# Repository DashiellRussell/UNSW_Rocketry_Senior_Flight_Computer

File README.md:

# UNSW Rocketry Senior Flight Computer

KiCad project for the senior flight computer used by UNSW Rocketry.

## Revisions

This repo holds each hardware revision in its own self-contained folder. Every
folder is a complete KiCad project (schematic, PCB, and its own copy of the
footprint library) so any revision can be opened and fabricated independently.

| Revision | Folder | Status |
| --- | --- | --- |
| **v0.0** | [`v0.0/`](v0.0/) | Frozen — known-good design. Do not edit. |
| **v1.0** | [`v1.0/`](v1.0/) | In progress — next revision (component + design changes). |

The exact v0.0 snapshot is also recoverable from the `v0.0` git tag
(`git checkout v0.0`).

> **Working on a new revision?** Copy the latest frozen folder to the next
> version number (e.g. `cp -R v1.0 v1.1`), then edit the copy. Tag the old one
> before you move on.

## Documents

Reference docs live in [`docs/`](docs/) and render inline on GitHub:

- [Schematic (PDF)](docs/UNSW_Rocketry_Senior_Flight_Computer.pdf) — exported full schematic (v0.0)
- [Project OZONE](docs/Project%20OZONE.pdf)

## Project layout (within each revision folder)

| File | Purpose |
| --- | --- |
| `UNSW_Rocketry_Senior_Flight_Computer.kicad_pro` | KiCad project file |
| `UNSW_Rocketry_Senior_Flight_Computer.kicad_sch` | Top-level schematic |
| `UNSW_Rocketry_Senior_Flight_Computer.kicad_pcb` | PCB layout |
| `Power.kicad_sch` | Power sheet |
| `Pyros.kicad_sch` | Pyrotechnic channels sheet |
| `Comms.kicad_sch` | Communications sheet |
| `Peripherals.kicad_sch` | Peripherals sheet |
| `Indication.kicad_sch` | Status / indication sheet |
| `UNSW_ROCKETRY_LIBRARY.pretty/` | Project-specific footprint library |
| `UNSW_Rocketry_Senior_Flight_Computer.csv` | BOM export |

## Opening the project

1. Install [KiCad 10.0](https://www.kicad.org/download/) or newer.
2. Clone this repo.
3. Open the `.kicad_pro` inside the revision folder you want, e.g.
   `v1.0/UNSW_Rocketry_Senior_Flight_Computer.kicad_pro`.

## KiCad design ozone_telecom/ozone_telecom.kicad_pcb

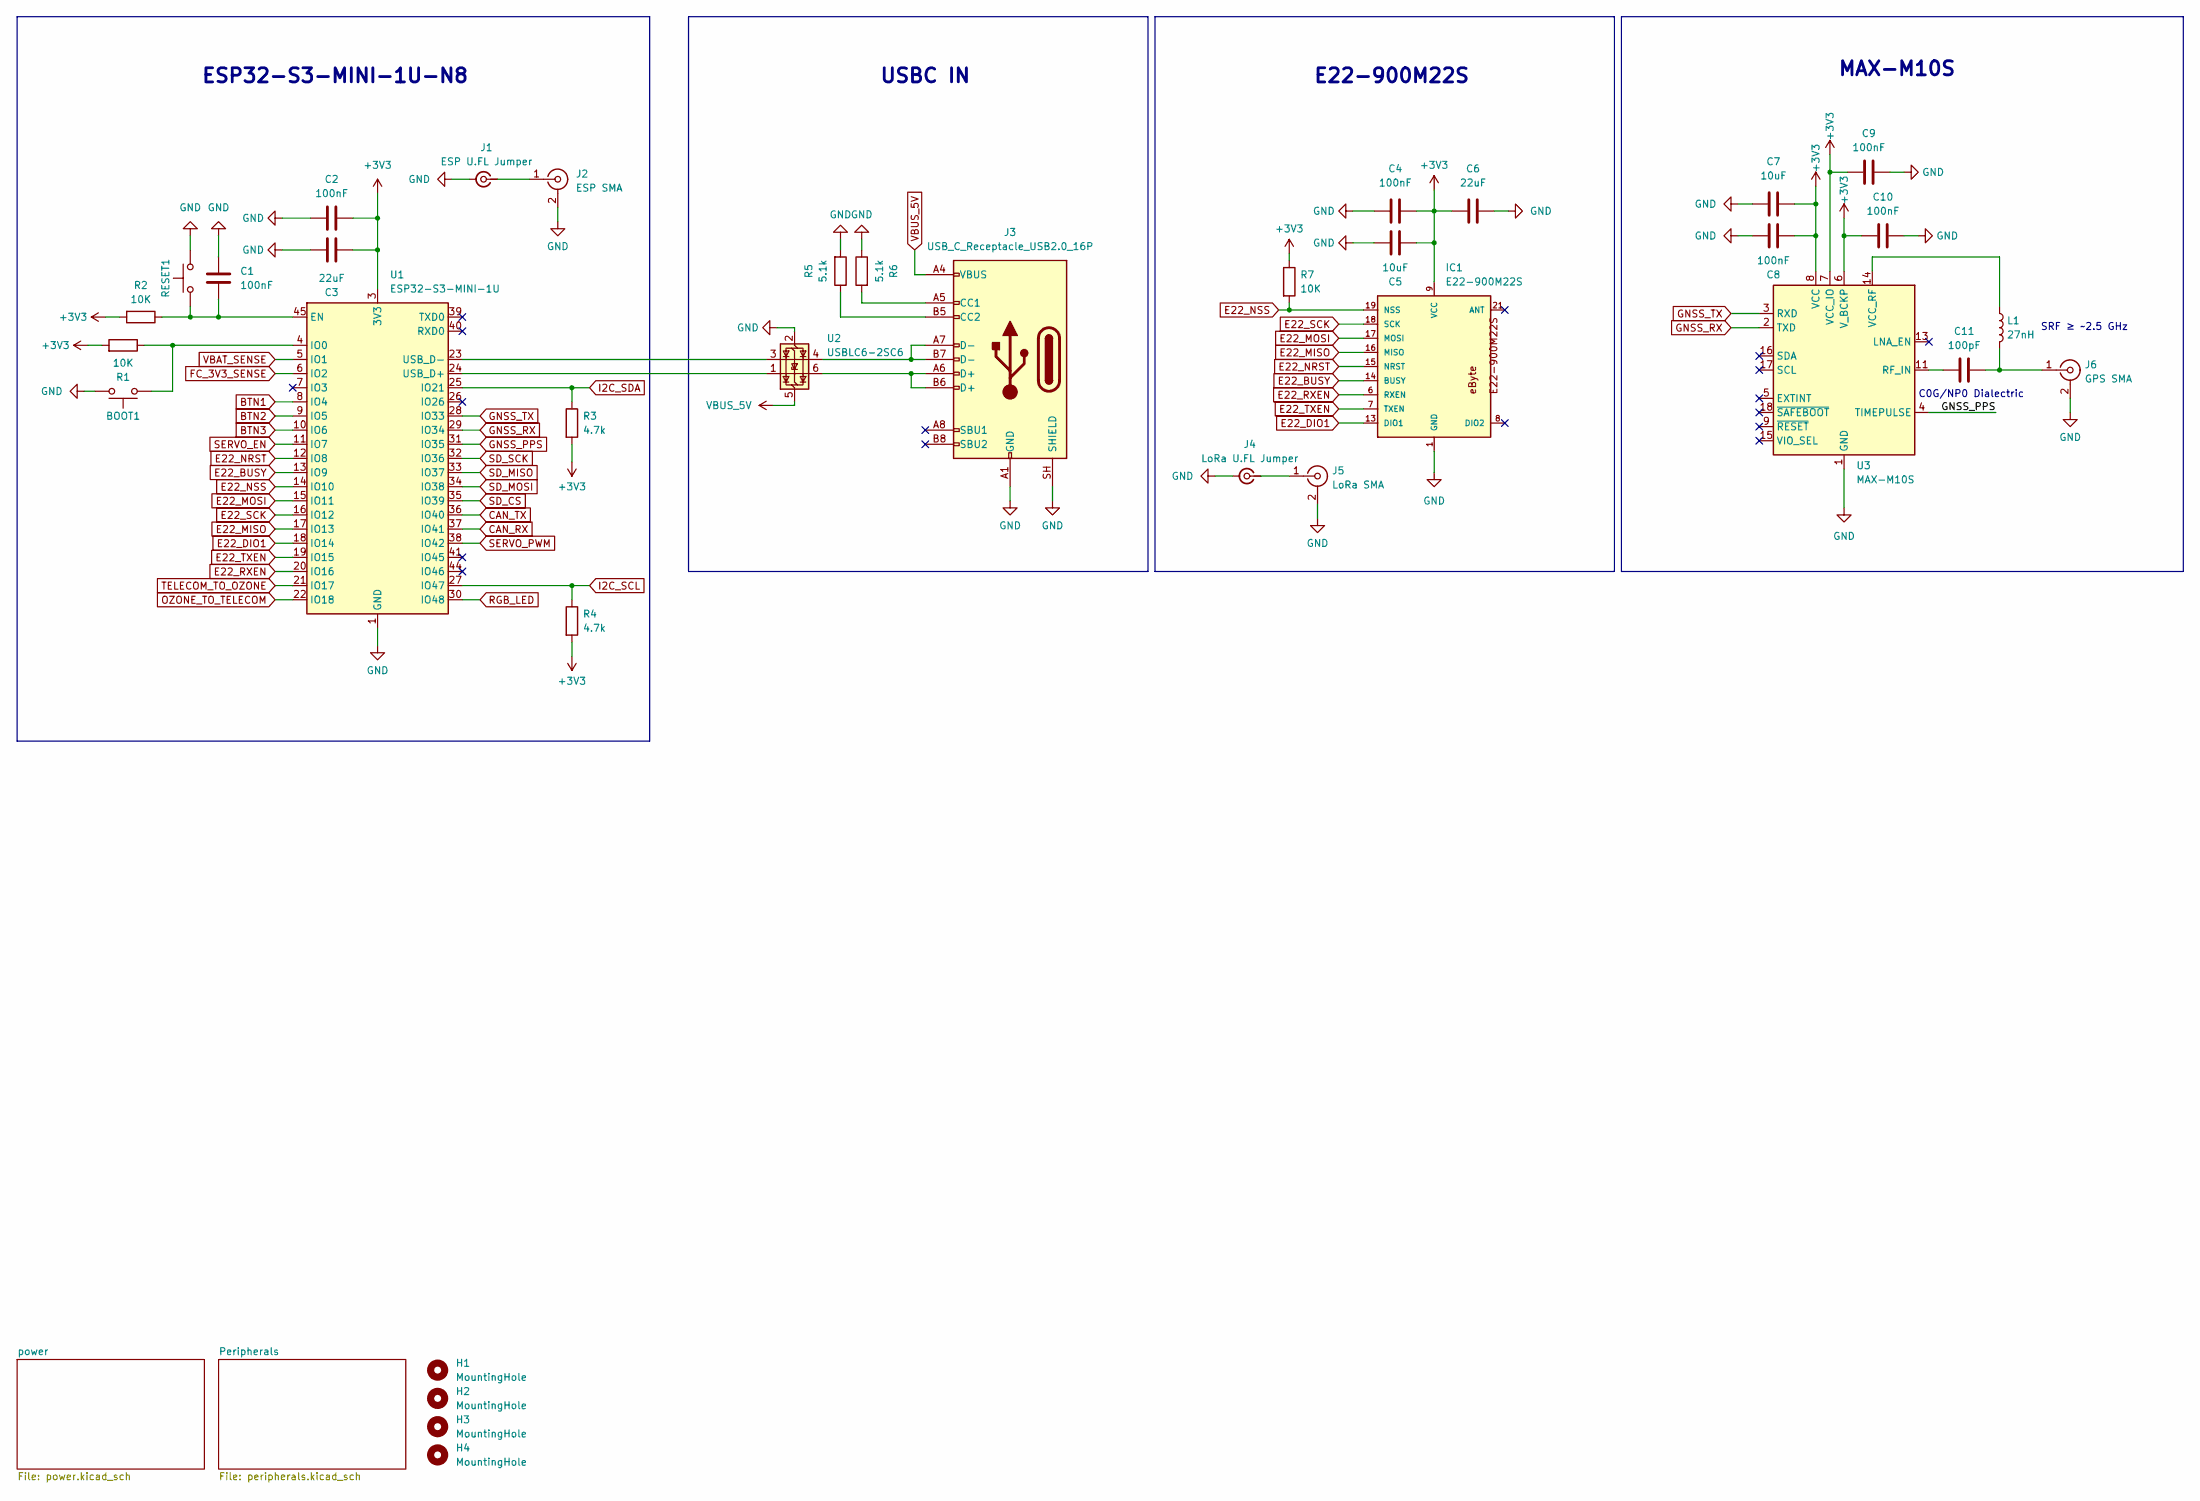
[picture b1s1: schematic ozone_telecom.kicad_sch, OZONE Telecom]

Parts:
BOOT1: SMD_4.6x2.8mm_h1.9mm; Push_SMD_4.6x2.8mm_h1.9mm
C1: 100nF; C_0603_1608Metric
C2, C4, C8, C9, C10: 100nF; C_0805_2012Metric
C3, C6: 22uF; C_0805_2012Metric
C5, C7: 10uF; C_0805_2012Metric
C11: 100pF; C_0603_1608Metric
H1, H2, H3, H4: MountingHole; MountingHole_3.2mm_M3_DIN965_Pad
IC1: E22-900M22S
J1: ESP U.FL Jumper; U.FL_Hirose_U.FL-R-SMT-1_Vertical
J2: ESP SMA; SMA_Amphenol_132289_EdgeMount
J3: USB_C_Receptacle_USB2.0_16P; USB_C_Receptacle_GCT_USB4085
J4: LoRa U.FL Jumper; U.FL_Hirose_U.FL-R-SMT-1_Vertical
J5: LoRa SMA; SMA_Amphenol_132289_EdgeMount
J6: GPS SMA; SMA_Amphenol_132289_EdgeMount
L1: 27nH; L_0603_1608Metric
R1, R2, R7: 10K; R_0603_1608Metric
R3, R4: 4.7k; R_0603_1608Metric
R5, R6: 5.1k; R_0603_1608Metric
RESET1: SMD_4.6x2.8mm_h1.9mm; Push_SMD_4.6x2.8mm_h1.9mm
U1: ESP32-S3-MINI-1U; ESP32-S2-MINI-1U
U2: USBLC6-2SC6; SOT-23-6
U3: MAX-M10S; ublox_MAX

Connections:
+3V3: C2.1, C3.1, C4.2, C5.2, C6.1, C7.1, C8.1, C9.2, C10.2, IC1.9 (VCC), R1.2, R2.2, R3.2, R4.2, R7.1, U1.3 (3V3), U3.6 (V_BCKP), U3.7 (VCC_IO), U3.8 (VCC); also elsewhere on the board
BTN1: U1.8 (IO4); also elsewhere on the board
BTN2: U1.9 (IO5); also elsewhere on the board
BTN3: U1.10 (IO6); also elsewhere on the board
CAN_RX: U1.37 (IO41); also elsewhere on the board
CAN_TX: U1.36 (IO40); also elsewhere on the board
E22_BUSY: IC1.14 (BUSY), U1.13 (IO9)
E22_DIO1: IC1.13 (DIO1), U1.18 (IO14)
E22_MISO: IC1.16 (MISO), U1.17 (IO13)
E22_MOSI: IC1.17 (MOSI), U1.15 (IO11)
E22_NRST: IC1.15 (NRST), U1.12 (IO8)
E22_NSS: IC1.19 (NSS), R7.2, U1.14 (IO10)
E22_RXEN: IC1.6 (RXEN), U1.20 (IO16)
E22_SCK: IC1.18 (SCK), U1.16 (IO12)
E22_TXEN: IC1.7 (TXEN), U1.19 (IO15)
FC_3V3_SENSE: U1.6 (IO2); also elsewhere on the board
GND: BOOT1.2, C1.1, C2.2, C3.2, C4.1, C5.1, C6.2, C7.2, C8.2, C9.1, C10.1, IC1.1 (GND), IC1.2 (GND), IC1.3 (GND), IC1.4 (GND), IC1.5 (GND), IC1.10 (GND), IC1.11 (GND), IC1.12 (GND), IC1.20 (GND), IC1.22 (GND), J1.2 (Ext), J2.2 (Ext), J3.A1 (GND), J3.A12 (GND), J3.B1 (GND), J3.B12 (GND), J3.SH (SHIELD), J4.2 (Ext), J5.2 (Ext), J6.2 (Ext), R5.2, R6.1, RESET1.1, U1.1 (GND), U1.2 (GND), U1.42 (GND), U1.43 (GND), U1.46 (GND), U1.47 (GND), U1.48 (GND), U1.49 (GND), U1.50 (GND), U1.51 (GND), U1.52 (GND), U1.53 (GND), U1.54 (GND), U1.55 (GND), U1.56 (GND), U1.57 (GND), U1.58 (GND), U1.59 (GND), U1.60 (GND), U1.61 (GND), U1.62 (GND), U1.63 (GND), U1.64 (GND), U1.65 (GND), U2.2 (GND), U3.1 (GND), U3.10 (GND), U3.12 (GND); also elsewhere on the board
GNSS_PPS: U1.31 (IO35), U3.4 (TIMEPULSE)
GNSS_RX: U1.29 (IO34), U3.2 (TXD)
GNSS_TX: U1.28 (IO33), U3.3 (RXD)
I2C_SCL: R4.1, U1.27 (IO47); also elsewhere on the board
I2C_SDA: R3.1, U1.25 (IO21); also elsewhere on the board
unnamed: J1.1 (In), J2.1 (In)
unnamed: J3.A5 (CC1), R6.2
unnamed: J3.B5 (CC2), R5.1
unnamed: J3.A6 (D+), J3.B6 (D+), U2.6 (I/O1)
unnamed: J3.A7 (D-), J3.B7 (D-), U2.4 (I/O2)
unnamed: J4.1 (In), J5.1 (In)
unnamed: C11.1, J6.1 (In), L1.2
unnamed: C1.2, R2.1, RESET1.2, U1.45 (EN)
unnamed: BOOT1.1, R1.1, U1.4 (IO0)
unnamed: U1.24 (USB_D+), U2.1 (I/O1)
unnamed: U1.23 (USB_D-), U2.3 (I/O2)
unnamed: C11.2, U3.11 (RF_IN)
unnamed: L1.1, U3.14 (VCC_RF)
OZONE_TO_TELECOM: U1.22 (IO18); also elsewhere on the board
RGB_LED: U1.30 (IO48); also elsewhere on the board
SD_CS: U1.35 (IO39); also elsewhere on the board
SD_MISO: U1.33 (IO37); also elsewhere on the board
SD_MOSI: U1.34 (IO38); also elsewhere on the board
SD_SCK: U1.32 (IO36); also elsewhere on the board
SERVO_EN: U1.11 (IO7); also elsewhere on the board
SERVO_PWM: U1.38 (IO42); also elsewhere on the board
TELECOM_TO_OZONE: U1.21 (IO17); also elsewhere on the board
VBAT_SENSE: U1.5 (IO1); also elsewhere on the board
VBUS_5V: J3.A4 (VBUS), J3.A9 (VBUS), J3.B4 (VBUS), J3.B9 (VBUS), U2.5 (VBUS); also elsewhere on the board

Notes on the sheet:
SRF ≥ ~2.5 GHz
E22-900M22S
C0G/NP0 Dialectric
ESP32-S3-MINI-1U-N8
MAX-M10S
USBC IN

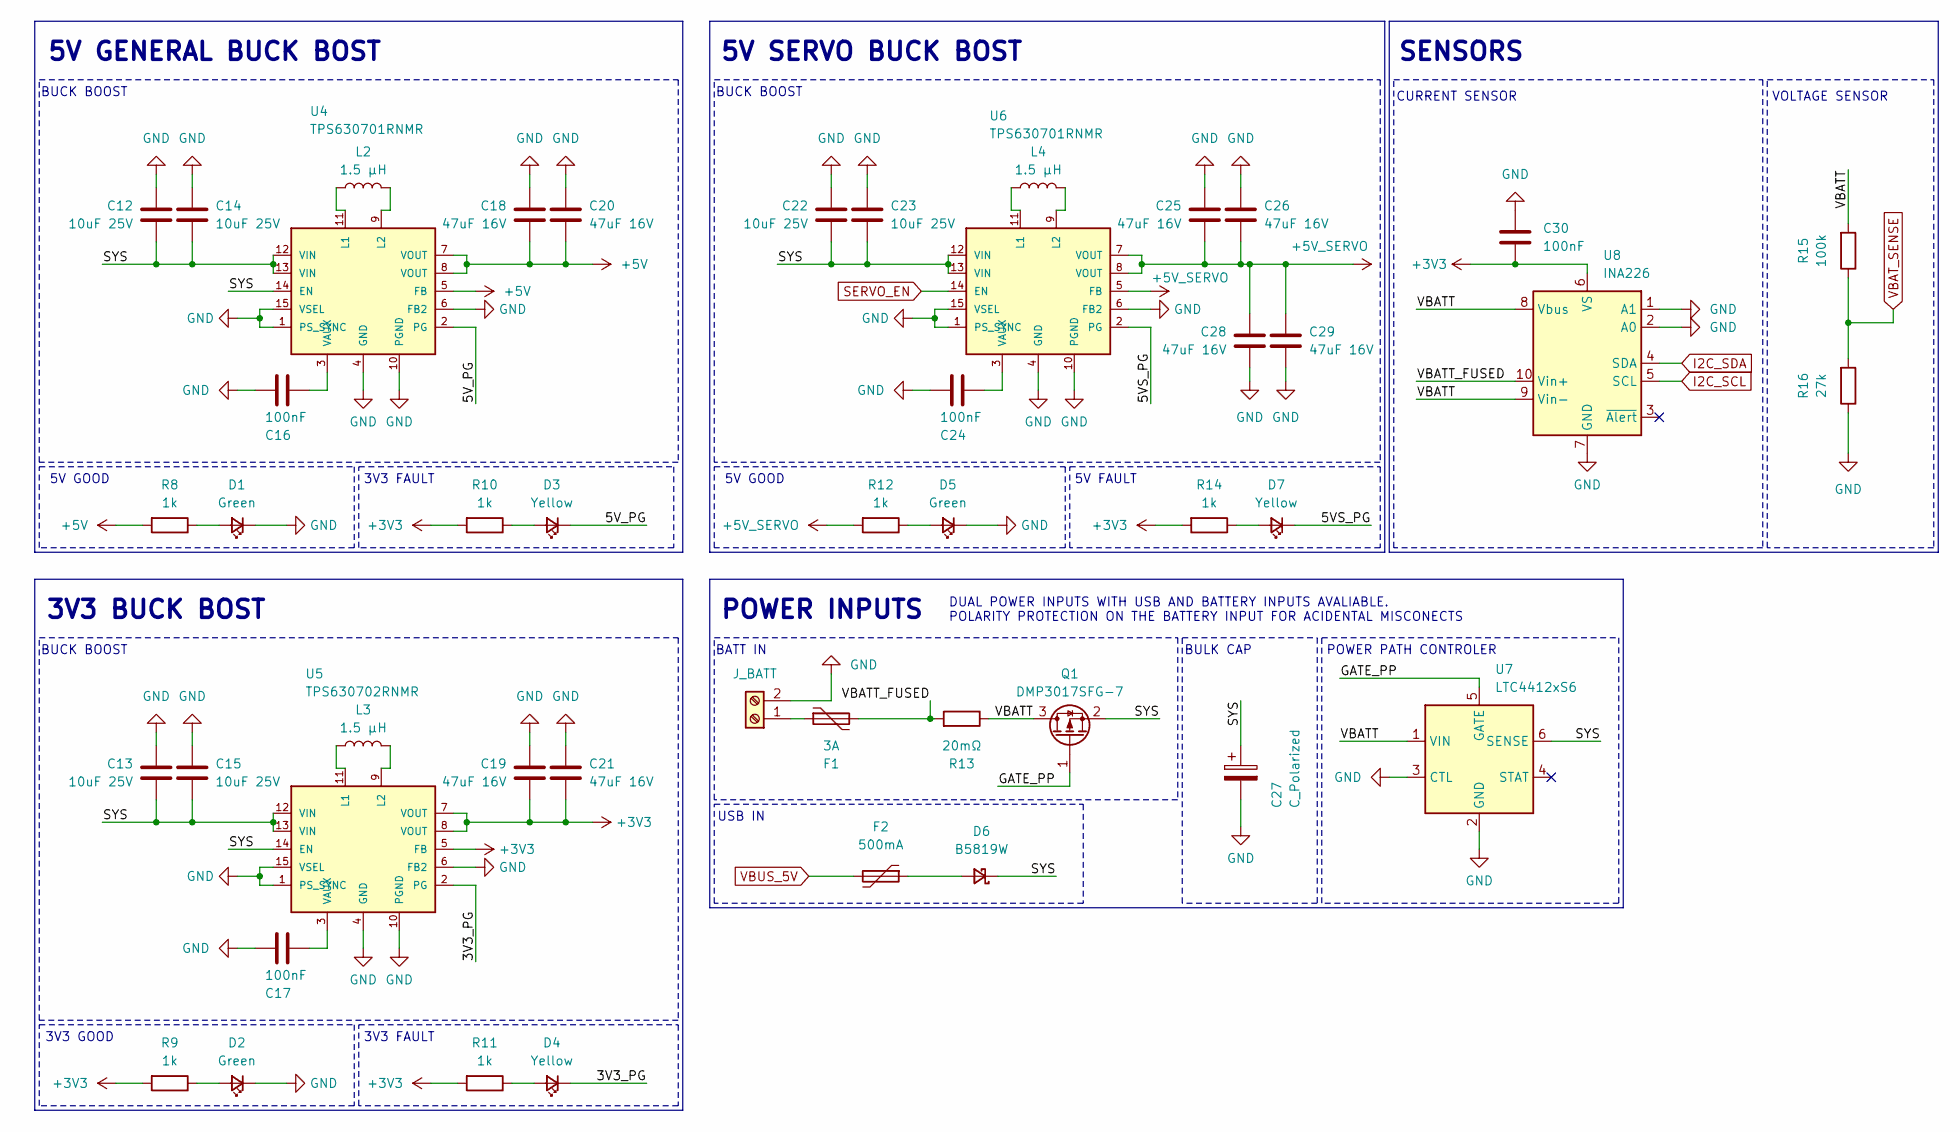
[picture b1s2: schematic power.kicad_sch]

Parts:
C12, C13, C14, C15, C22, C23: 10uF 25V; C_0805_2012Metric
C16, C17, C24, C30: 100nF; C_0805_2012Metric
C18, C19, C20, C21, C25, C26, C28, C29: 47uF 16V; C_0805_2012Metric
C27: C_Polarized; CP_Elec_6.3x5.4
D1, D2, D5: Green; LED_0603_1608Metric_Green
D3, D4, D7: Yellow; LED_0603_1608Metric_Yellow
D6: B5819W; D_SOD-123
F1: 3A; Fuse_1206_3216Metric
F2: 500mA; Fuse_1206_3216Metric
J7: J_BATT; TerminalBlock_Phoenix_PT-1,5-2-3.5-H_1x02_P3.50mm_Horizontal
L2, L3, L4: 1.5 µH; L_Coilcraft_XxL4020
Q1: DMP3017SFG-7; SOT-23
R8, R9, R10, R11, R12, R14: 1k; R_0603_1608Metric
R13: 20mΩ; R_2512_6332Metric
R15: 100k; R_0603_1608Metric
R16: 27k; R_0603_1608Metric
U4, U6: TPS630701RNMR; RNM0015A
U5: TPS630702RNMR; RNM0015A
U7: LTC4412xS6; TSOT-23-6
U8: INA226; TSSOP-10_3x3mm_P0.5mm

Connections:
+3V3: C19.2, C21.2, C30.2, R9.2, R10.2, R11.2, R14.2, U5.5 (FB), U5.7 (VOUT), U5.8 (VOUT), U8.6 (VS); also elsewhere on the board
+5V: C18.2, C20.2, R8.2, U4.5 (FB), U4.7 (VOUT), U4.8 (VOUT); also elsewhere on the board
+5V_SERVO: C25.2, C26.2, C28.1, C29.1, R12.2, U6.5 (FB), U6.7 (VOUT), U6.8 (VOUT); also elsewhere on the board
/power/3V3_PG: D4.1 (K), U5.2 (PG)
/power/5VS_PG: D7.1 (K), U6.2 (PG)
/power/5V_PG: D3.1 (K), U4.2 (PG)
/power/GATE_PP: Q1.1 (G), U7.5 (GATE)
/power/SYS: C12.2, C13.2, C14.2, C15.2, C22.2, C23.2, C27.1, D6.1 (K), Q1.2 (S), U4.12 (VIN), U4.13 (VIN), U4.14 (EN), U5.12 (VIN), U5.13 (VIN), U5.14 (EN), U6.12 (VIN), U6.13 (VIN), U7.6 (SENSE)
/power/VBATT: Q1.3 (D), R13.1, R15.2, U7.1 (VIN), U8.8 (Vbus), U8.9 (Vin-)
/power/VBATT_FUSED: F1.2, R13.2, U8.10 (Vin+)
GND: C12.1, C13.1, C14.1, C15.1, C16.2, C17.2, C18.1, C19.1, C20.1, C21.1, C22.1, C23.1, C24.2, C25.1, C26.1, C27.2, C28.2, C29.2, C30.1, D1.1 (K), D2.1 (K), D5.1 (K), J7.2, R16.1, U4.1 (PS_SYNC), U4.4 (GND), U4.6 (FB2), U4.10 (PGND), U4.15 (VSEL), U5.1 (PS_SYNC), U5.4 (GND), U5.6 (FB2), U5.10 (PGND), U5.15 (VSEL), U6.1 (PS_SYNC), U6.4 (GND), U6.6 (FB2), U6.10 (PGND), U6.15 (VSEL), U7.2 (GND), U7.3 (CTL), U8.1 (A1), U8.2 (A0), U8.7 (GND); also elsewhere on the board
I2C_SCL: U8.5 (SCL); also elsewhere on the board
I2C_SDA: U8.4 (SDA); also elsewhere on the board
unnamed: D1.2 (A), R8.1
unnamed: D2.2 (A), R9.1
unnamed: D3.2 (A), R10.1
unnamed: D4.2 (A), R11.1
unnamed: D5.2 (A), R12.1
unnamed: D6.2 (A), F2.1
unnamed: D7.2 (A), R14.1
unnamed: F1.1, J7.1
unnamed: L2.1, U4.11 (L1)
unnamed: L2.2, U4.9 (L2)
unnamed: C16.1, U4.3 (VAUX)
unnamed: L3.1, U5.11 (L1)
unnamed: L3.2, U5.9 (L2)
unnamed: C17.1, U5.3 (VAUX)
unnamed: L4.1, U6.11 (L1)
unnamed: L4.2, U6.9 (L2)
unnamed: C24.1, U6.3 (VAUX)
SERVO_EN: U6.14 (EN); also elsewhere on the board
VBAT_SENSE: R15.1, R16.2; also elsewhere on the board
VBUS_5V: F2.2; also elsewhere on the board

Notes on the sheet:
POWER PATH CONTROLER
VOLTAGE SENSOR
SENSORS
5V FAULT
BUCK BOOST
3V3 FAULT
BATT IN
3V3 GOOD
3V3 BUCK BOST
5V GOOD
USB IN
BULK CAP
POWER INPUTS
CURRENT SENSOR
5V GENERAL BUCK BOST
5V SERVO BUCK BOST
DUAL POWER INPUTS WITH USB AND BATTERY INPUTS AVALIABLE. POLARITY PROTECTION ON THE BATTERY INPUT FOR ACIDENTAL MISCONECTS

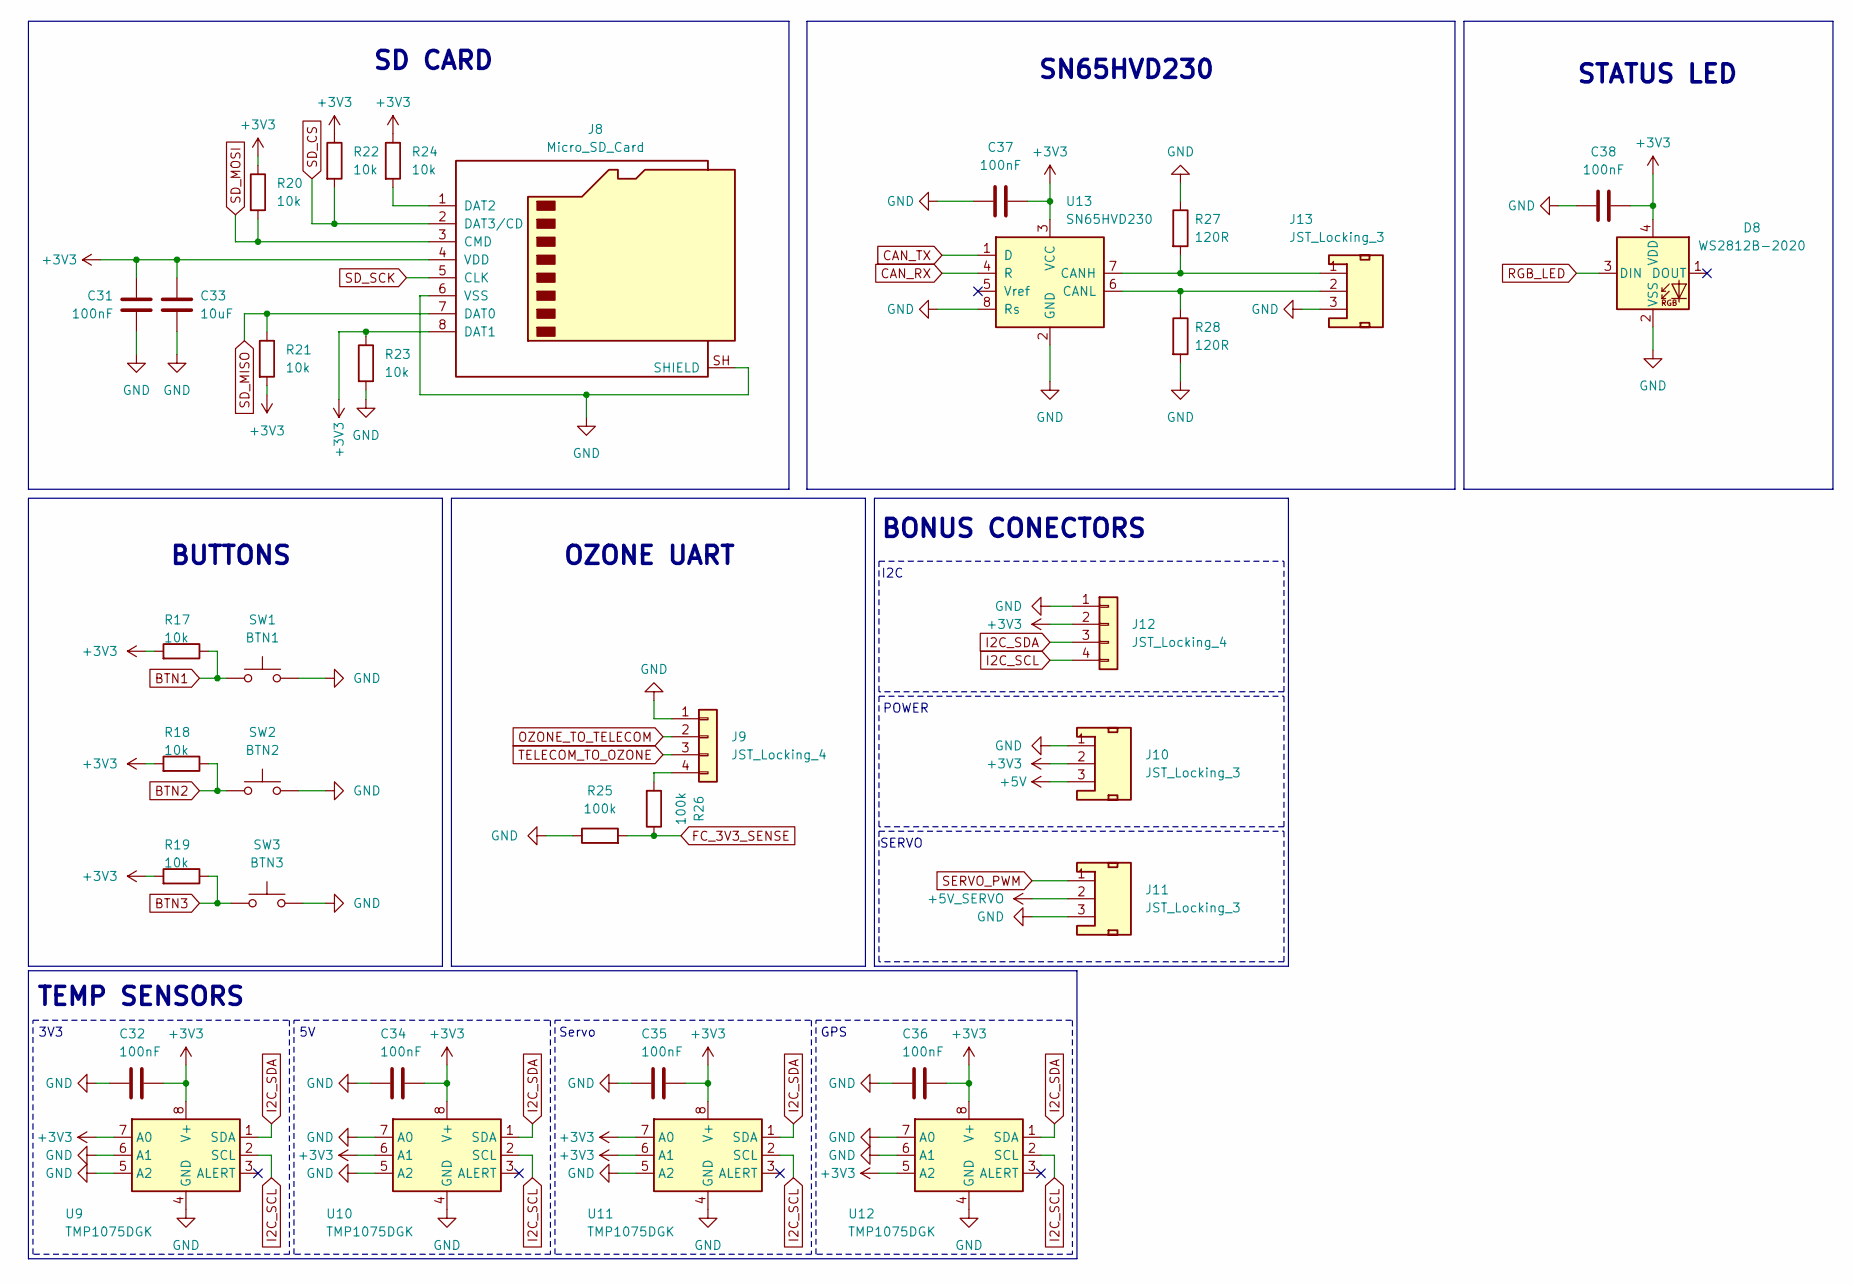
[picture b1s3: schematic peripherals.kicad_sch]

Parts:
C31, C32, C34, C35, C36: 100nF; C_0805_2012Metric
C33: 10uF; C_0805_2012Metric
C37, C38: 100nF; C_0603_1608Metric
D8: WS2812B-2020; LED_WS2812B-2020_PLCC4_2.0x2.0mm
J8: Micro_SD_Card; microSD_HC_Molex_47219-2001
J9, J12: JST_Locking_4; JST_1x04_P1.25mm_Locking_Horizontal_SMD
J10, J11, J13: JST_Locking_3; JST_1x03_P1.25mm_Locking_Horizontal_SMD
R17, R18, R19, R20, R21, R22, R23, R24: 10k; R_0603_1608Metric
R25, R26: 100k; R_0603_1608Metric
R27, R28: 120R; C_0805_2012Metric
SW1: BTN1; SW_Push_1P1T_NO_CK_KMR2
SW2: BTN2; SW_Push_1P1T_NO_CK_KMR2
SW3: BTN3; SW_Push_1P1T_NO_CK_KMR2
U9, U10, U11, U12: TMP1075DGK; VSSOP-8_3x3mm_P0.65mm
U13: SN65HVD230; SOIC-8_3.9x4.9mm_P1.27mm

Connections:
+3V3: C31.1, C32.1, C33.1, C34.1, C35.1, C36.1, C37.1, C38.1, D8.4 (VDD), J8.4 (VDD), J8.8 (DAT1), J10.2, J12.2, R17.2, R18.2, R19.2, R20.1, R21.2, R22.1, R23.1, R24.1, U9.7 (A0), U9.8 (V+), U10.6 (A1), U10.8 (V+), U11.6 (A1), U11.7 (A0), U11.8 (V+), U12.5 (A2), U12.8 (V+), U13.3 (VCC); also elsewhere on the board
+5V: J10.3; also elsewhere on the board
+5V_SERVO: J11.2; also elsewhere on the board
BTN1: R17.1, SW1.1; also elsewhere on the board
BTN2: R18.1, SW2.1; also elsewhere on the board
BTN3: R19.1, SW3.1; also elsewhere on the board
CAN_RX: U13.4 (R); also elsewhere on the board
CAN_TX: U13.1 (D); also elsewhere on the board
FC_3V3_SENSE: R25.2, R26.1; also elsewhere on the board
GND: C31.2, C32.2, C33.2, C34.2, C35.2, C36.2, C37.2, C38.2, D8.2 (VSS), J8.6 (VSS), J8.SH (SHIELD), J9.1, J10.1, J11.3, J12.1, J13.3, R23.2, R25.1, R27.1, R28.2, SW1.2, SW2.2, SW3.2, U9.4 (GND), U9.5 (A2), U9.6 (A1), U10.4 (GND), U10.5 (A2), U10.7 (A0), U11.4 (GND), U11.5 (A2), U12.4 (GND), U12.6 (A1), U12.7 (A0), U13.2 (GND), U13.8 (Rs); also elsewhere on the board
I2C_SCL: J12.4, U9.2 (SCL), U10.2 (SCL), U11.2 (SCL), U12.2 (SCL); also elsewhere on the board
I2C_SDA: J12.3, U9.1 (SDA), U10.1 (SDA), U11.1 (SDA), U12.1 (SDA); also elsewhere on the board
unnamed: J8.1 (DAT2), R24.2
unnamed: J9.4, R26.2
unnamed: J13.1, R27.2, U13.7 (CANH)
unnamed: J13.2, R28.1, U13.6 (CANL)
OZONE_TO_TELECOM: J9.2; also elsewhere on the board
RGB_LED: D8.3 (DIN); also elsewhere on the board
SD_CS: J8.2 (DAT3/CD), R22.2; also elsewhere on the board
SD_MISO: J8.7 (DAT0), R21.1; also elsewhere on the board
SD_MOSI: J8.3 (CMD), R20.2; also elsewhere on the board
SD_SCK: J8.5 (CLK); also elsewhere on the board
SERVO_PWM: J11.1; also elsewhere on the board
TELECOM_TO_OZONE: J9.3; also elsewhere on the board

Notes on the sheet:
STATUS LED
Servo
BONUS CONECTORS
TEMP SENSORS
I2C
POWER
3V3
BUTTONS
SN65HVD230
OZONE UART
SD CARD
SERVO
GPS

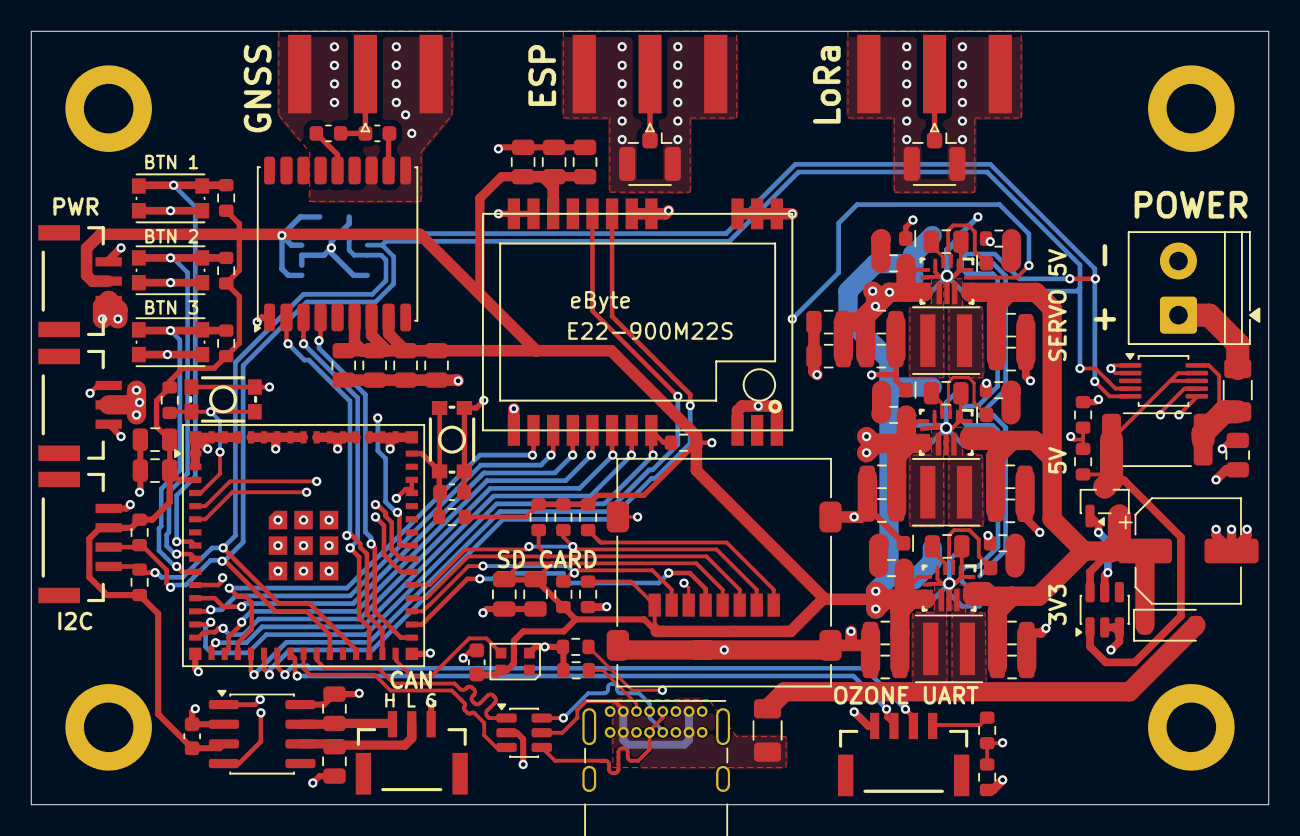
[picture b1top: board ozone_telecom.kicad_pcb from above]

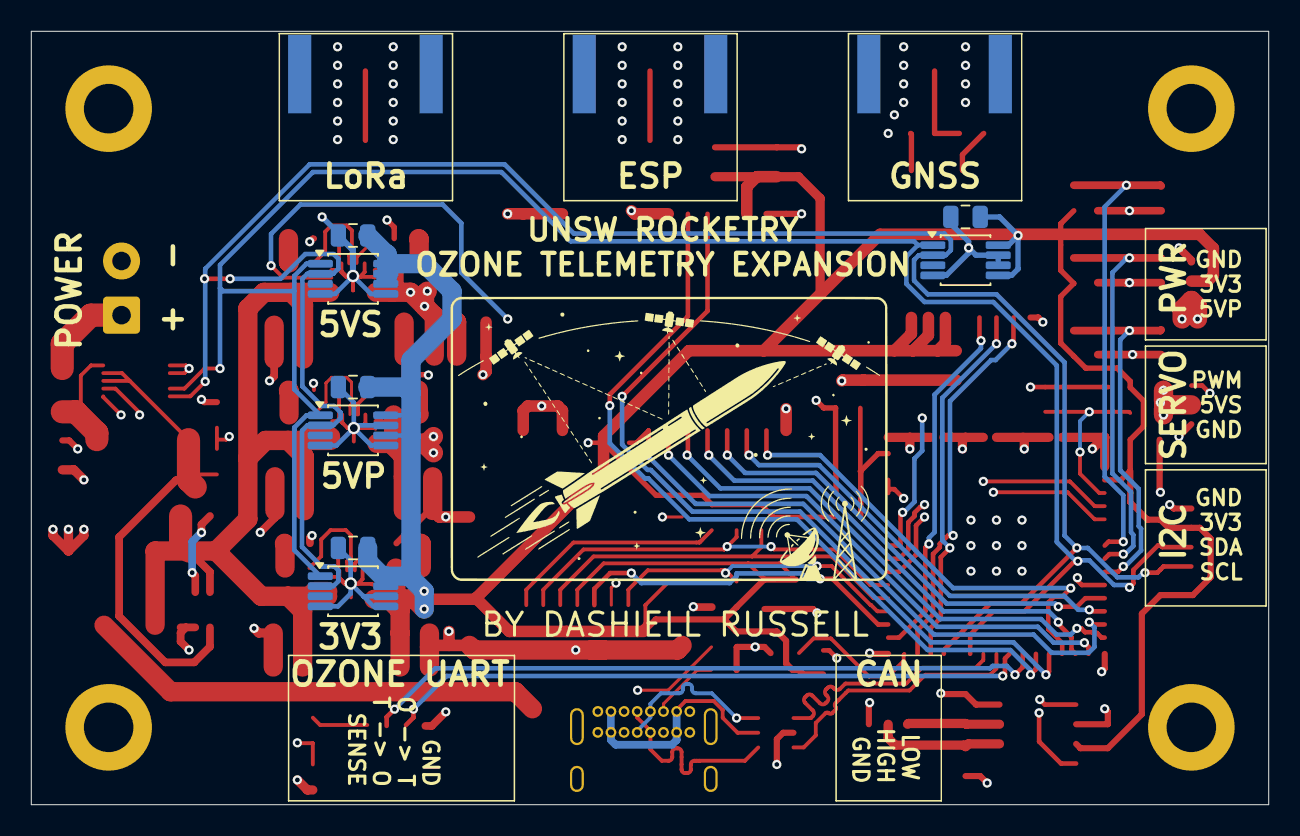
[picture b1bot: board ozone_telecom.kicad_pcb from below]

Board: 4 copper layers, 80.0 x 50.0 mm, 117 parts (8 on the bottom side), 76 nets.

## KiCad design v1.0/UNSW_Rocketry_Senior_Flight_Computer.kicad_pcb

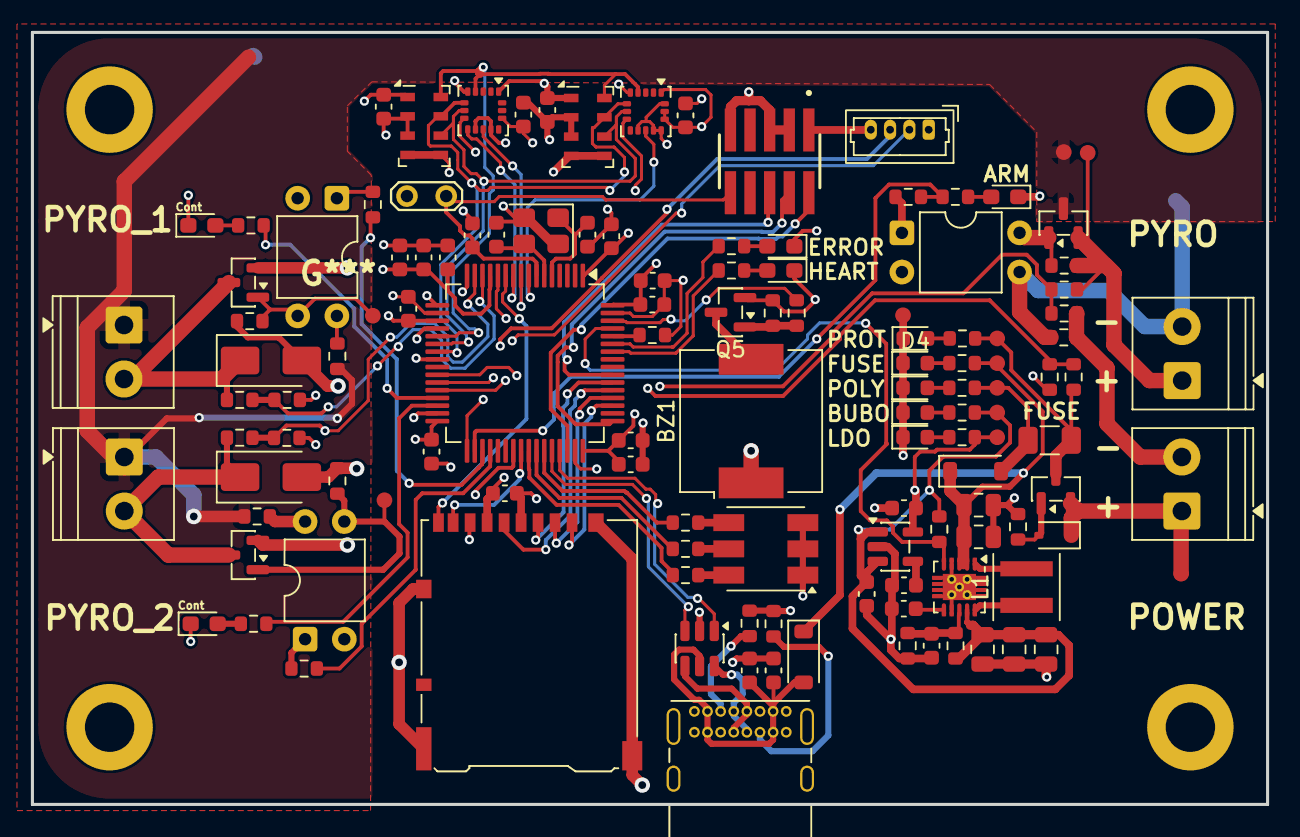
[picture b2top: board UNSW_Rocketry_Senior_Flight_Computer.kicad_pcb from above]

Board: 4 copper layers, 80.0 x 50.0 mm, 129 parts (0 on the bottom side), 90 nets.

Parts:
BZ1: Buzzer; Buzzer_CUI_CPT-9019S-SMT
C1, C2: 27pF; C_0603_1608Metric
C3, C5, C6, C8, C10, C11, C13, C17, C24, C25, C26, C27, C28, C30: 0.1uF; C_0603_1608Metric
C4, C9, C21, C22, C29: 1.0uF; C_0603_1608Metric
C7, C23: 10nF; C_0603_1608Metric
C12: 4.7uF; C_0603_1608Metric
C14, C15: 10uF; C_0805_2012Metric
C16, C18, C20: 22uF; C_0805_2012Metric
C19: 10pF; C_0603_1608Metric
D1: 5.1V; D_SOD-323
D2, D8: B5819W; D_SOD-123
D3, D4, D5, D6, D7: Green; LED_0603_1608Metric
D9, D15: LED_RED; LED_0603_1608Metric_Pad1.05x0.95mm_HandSolder
D10, D12: LED_YELLOW; LED_0603_1608Metric_Pad1.05x0.95mm_HandSolder
D11, D13: SMAJ15A; D_SMA
D14: LED_RGB; LED_RGB_5050-6
D16: LED_GREEN; LED_0603_1608Metric_Pad1.05x0.95mm_HandSolder
F1: 1A; Fuse_1206_3216Metric
H1, H2, H3, H4: MountingHole; MountingHole_3.2mm_M3_DIN965_Pad
J1: SWD; SAMTEC_FTSH-105-01-X-DV-K-X
J2: Micro_SD_Card_Det1; microSD_HC_Hirose_DM3AT-SF-PEJM5
J3: USB_C_Receptacle_USB2.0_16P; USB_C_Receptacle_GCT_USB4085
J5: Conn_01x04; Molex_PicoBlade_53047-0410_1x04_P1.25mm_Vertical
J7: J_PYRO1; TerminalBlock_Phoenix_PT-1,5-2-3.5-H_1x02_P3.50mm_Horizontal
J8: J_PYRO2; TerminalBlock_Phoenix_PT-1,5-2-3.5-H_1x02_P3.50mm_Horizontal
J9: J_PYRO_BAT; TerminalBlock_Phoenix_PT-1,5-2-3.5-H_1x02_P3.50mm_Horizontal
J10: J_BATT; TerminalBlock_Phoenix_PT-1,5-2-3.5-H_1x02_P3.50mm_Horizontal
JP1: RESET_JMP; TestPoint_2Pads_Pitch2.54mm_Drill0.8mm
L1: 1µH; L_Coilcraft_XxL4020
Q1: DMG2301L; SOT-23
Q2: AO3401A; SOT-23
Q3, Q4, Q5: AO3400A; SOT-23
R1, R6, R15, R22, R23, R25, R28, R29, R31, R37: 10k; R_0603_1608Metric
R2: 620k; R_0603_1608Metric
R3, R4, R5, R21: 100k; R_0603_1608Metric
R7: 33k; R_0603_1608Metric
R8, R9, R10: 4.7k; R_0603_1608Metric
R11, R12, R19, R24, R30, R38, R39: 1k; R_0603_1608Metric
R13, R14: 5.1k; R_0603_1608Metric
R16, R26, R32: 3.3k; R_0603_1608Metric
R17: 0; R_0603_1608Metric
R18, R20, R27: 330; R_0603_1608Metric
R33, R34, R35: 100; R_0603_1608Metric
R36: 150; R_0603_1608Metric
TP1, TP2, TP3, TP4, TP5, TP6, TP7, TP8, TP9, TP10, TP12: 1.0mm; TestPoint-1.0mm
U1: STM32L452RETx; LQFP-64_10x10mm_P0.5mm
U2: TPS63060; Texas_S-PWSON-N10_ThermalVias
U3: SPX3819M5-L-3-3; SOT-23-5
U4: H3LIS331DL; LGA-16_3x3mm_P0.5mm_LayoutBorder3x5y
U5: MS5611 #1; LGA-8_3x5mm_P1.25mm
U6: LIS3DH; LGA-16_3x3mm_P0.5mm_LayoutBorder3x5y
U7: MS5611 #2; LGA-8_3x5mm_P1.25mm
U8: USBLC6-2SC6; SOT-23-6
U9, U10, U11: PC817; DIP-4_W7.62mm
Y1: 8MHz; Crystal_SMD_3225-4Pin_3.2x2.5mm

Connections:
+3.3V: BZ1.1 (+), C4.2, C5.2, C6.1, C7.2, C8.2, C9.1, C10.2, C11.2, C12.2, C13.2, C22.2, C24.2, C25.1, C26.2, C27.1, C28.2, J1.01, J2.4 (VDD), J5.4, R12.1, TP5.1 (1_1), U1.1 (VBAT), U1.13 (VDDA), U1.19 (VDD), U1.32 (VDD), U1.48 (VDDUSB), U1.64 (VDD), U3.5 (OUT), U4.1 (VDD_IO), U4.14 (VDD), U4.15 (VDD), U5.1 (VDD), U6.1 (VDD_IO), U6.14 (VDD), U7.1 (VDD)
+3.6V: C16.2, C18.2, C20.2, C21.1, R2.1, R3.1, R11.1, TP2.1 (1_1), U2.9 (VOUT), U3.1 (IN), U3.3 (EN)
/Comms/USB_RAW_N: J3.A7 (D-), J3.B7 (D-), U8.4 (I/O2)
/Comms/USB_RAW_P: J3.A6 (D+), J3.B6 (D+), U8.6 (I/O1)
/Power/VBAT_POLY_STATUS: D2.2 (A), F1.1, R10.1, TP6.1 (1_1)
BUZZER: R33.1, U1.62 (PB9)
CS_H3LIS: U1.26 (PB0), U4.8 (CS)
CS_LIS3DH: U1.27 (PB1), U6.8 (CS)
CS_MS5611_1: U1.28 (PB2), U5.4 (CSB), U5.5 (CSB)
CS_MS5611_2: U1.33 (PB12), U7.4 (CSB), U7.5 (CSB)
GND: C1.2, C2.1, C3.1, C4.1, C5.1, C6.2, C7.1, C8.1, C9.2, C10.1, C11.1, C12.1, C13.1, C14.1, C15.2, C16.1, C17.1, C18.1, C19.2, C20.1, C21.2, C22.1, C23.1, C24.1, C25.2, C26.1, C27.2, C28.1, C29.1, C30.1, D3.1 (K), D4.1 (K), D5.1 (K), D6.1 (K), D7.1 (K), D9.1 (K), D10.1 (K), D12.1 (K), D14.1 (RK), D14.2 (GK), D14.3 (BK), D15.1 (K), D16.1 (K), J1.03, J1.05, J1.09, J2.6 (VSS), J2.SH (SHIELD), J3.A1 (GND), J3.A12 (GND), J3.B1 (GND), J3.B12 (GND), J3.SH (SHIELD), J5.1, J10.2, JP1.2 (B), Q5.2 (S), R1.2, R4.1, R5.2, R6.2, R13.2, R14.2, R16.2, R17.1, R26.1, R32.1, R37.1, TP4.1 (1_1), U1.12 (VSSA), U1.18 (VSS), U1.31 (VSS), U1.47 (VSS), U1.63 (VSS), U2.4 (PS/SYNC), U2.7 (GND), U2.11 (PGND), U3.2 (GND), U4.5 (GND), U4.10 (GND), U4.12 (GND), U4.13 (GND), U4.16 (GND), U5.2 (PS), U5.3 (GND), U6.5 (GND), U6.10 (GND), U6.12 (GND), U7.2 (PS), U7.3 (GND), U8.2 (GND), U9.2, U10.2, U11.2, Y1.2 (G), Y1.4 (G)
INT1_H3LIS: U1.8 (PC0), U4.11 (INT1)
INT1_LIS3DH: U1.9 (PC1), U6.11 (INT1)
INT2_LIS3DH: U1.10 (PC2), U6.9 (INT2)
LED_ERROR: R38.1, U1.59 (PB7)
LED_HEARTBEAT: R39.1, U1.58 (PB6)
NRST: C3.2, J1.10, JP1.1 (A), U1.7 (NRST)
unnamed: BZ1.2 (-), Q5.3 (D)
unnamed: D1.2 (A), Q1.1 (G), R5.1
unnamed: D3.2 (A), R8.2
unnamed: D4.2 (A), R9.2
unnamed: D5.2 (A), R10.2
unnamed: D6.2 (A), R11.2
unnamed: D7.2 (A), R12.2
unnamed: C29.2, C30.2, D8.2 (A), J3.A4 (VBUS), J3.A9 (VBUS), J3.B4 (VBUS), J3.B9 (VBUS), U8.5 (VBUS)
unnamed: D9.2 (A), R19.1
unnamed: D10.2 (A), R24.1
unnamed: D11.1 (A1), J7.2, Q3.3 (D), R25.2
unnamed: D12.2 (A), R30.1
unnamed: D13.1 (A1), J8.2, Q4.3 (D), R31.2
unnamed: D14.4 (BA), R34.2
unnamed: D14.5 (GA), R35.2
unnamed: D14.6 (RA), R36.2
unnamed: D15.2 (A), R38.2
unnamed: D16.2 (A), R39.2
unnamed: J3.A5 (CC1), R13.1
unnamed: J3.B5 (CC2), R14.1
unnamed: Q2.1 (G), R21.1, U9.4
unnamed: Q3.1 (G), R23.1, TP10.1 (1_1), U10.3
unnamed: Q4.1 (G), R29.1, TP12.1 (1_1), U11.3
unnamed: Q5.1 (G), R33.2, R37.2
unnamed: R18.2, U9.1
unnamed: R20.2, U10.1
unnamed: R22.2, U10.4
unnamed: R27.2, U11.1
unnamed: R28.2, U11.4
unnamed: C2.2, U1.5 (PH0), Y1.1
unnamed: C1.1, U1.6 (PH1), Y1.3
unnamed: R1.1, U1.60 (PH3)
unnamed: C19.1, R2.2, R4.2, U2.8 (FB)
unnamed: L1.2, U2.1 (L1)
unnamed: L1.1, U2.10 (L2)
unnamed: C17.2, U2.6 (VAUX)
unnamed: C23.2, U3.4 (BP)
PG_BUCKBOOST: R3.2, U1.61 (PB8), U2.5 (PG)
PYRO1_CONT: R25.1, R26.2, U1.14 (PA0)
PYRO1_CONT_LED: R24.2, U1.29 (PB10)
PYRO1_GATE: R20.1, U1.35 (PB14)
PYRO2_CONT: R31.1, R32.2, U1.15 (PA1)
PYRO2_CONT_LED: R30.2, U1.30 (PB11)
PYRO2_GATE: R27.1, U1.36 (PB15)
PYRO_ARM: R18.1, R19.2, U1.34 (PB13)
PYRO_BATT: J7.1, J8.1, Q2.3 (D), R22.1, R28.1, TP9.1 (1_1)
PYRO_BATT_RAW: J9.1, Q2.2 (S), R15.1, R21.2, TP8.1 (1_1)
PYRO_BATT_SENSE: R15.2, R16.1, U1.20 (PA4)
PYRO_GND: D11.2 (A2), D13.2 (A2), J9.2, Q3.2 (S), Q4.2 (S), R17.2, R23.2, R29.2, U9.3
RGB_B: R34.1, U1.43 (PA10)
RGB_G: R35.1, U1.42 (PA9)
RGB_R: R36.1, U1.41 (PA8)
SDMMC_CLK: J2.5 (CLK), U1.53 (PC12)
SDMMC_CMD: J2.3 (CMD), U1.54 (PD2)
SDMMC_D0: J2.7 (DAT0), U1.39 (PC8)
SDMMC_D1: J2.8 (DAT1), U1.40 (PC9)
SDMMC_D2: J2.1 (DAT2), U1.51 (PC10)
SDMMC_D3: J2.2 (DAT3/CD), U1.52 (PC11)
SD_CD: J2.9 (DET), U1.11 (PC3)
SPI1_MISO: U1.22 (PA6), U4.7 (SDO), U5.6 (SDO), U6.7 (SDO), U7.6 (SDO)
SPI1_MOSI: U1.23 (PA7), U4.6 (SDI), U5.7 (SDI/SDA), U6.6 (SDI), U7.7 (SDI/SDA)
SPI1_SCK: U1.21 (PA5), U4.4 (SPC), U5.8 (SCLK), U6.4 (SPC), U7.8 (SCLK)
SWCLK: J1.04, U1.49 (PA14)
SWDIO: J1.02, U1.46 (PA13)
SWO: J1.06, U1.55 (PB3)
UART_RX: J5.3, U1.17 (PA3)
UART_TX: J5.2, U1.16 (PA2)
USB_N: U1.44 (PA11), U8.3 (I/O2)
USB_P: U1.45 (PA12), U8.1 (I/O1)
VBAT_FUSED: C14.2, C15.1, D2.1 (K), D8.1 (K), R9.1, TP7.1 (1_1), U2.2 (VIN), U2.3 (EN)
VBAT_PROT: F1.2, Q1.3 (S), R7.1, R8.1, TP3.1 (1_1)
VBAT_RAW: D1.1 (K), J10.1, Q1.2 (D), TP1.1 (1_1)
VBAT_SENSE: R6.1, R7.2, U1.24 (PC4)

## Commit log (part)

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2026-04-13 starting work
2026-04-18 feat: MCU setup
2026-04-18 feat: Power & comms
2026-04-19 feat: Comms complete
2026-04-19 feat: Pyro done
2026-04-19 feat: VBAT Sense
2026-04-19 feat: finish board (draft)
2026-04-19 feat: finish schematic (erc_pass)
2026-04-19 feat: finish schematic (Full)
2026-04-19 feat: BCB Start ( power & pyro done)
2026-04-22 feat: PCB Designed (Silk screen adjustments)
2026-06-01 fixes
2026-06-01 Fix: Tims review changes
